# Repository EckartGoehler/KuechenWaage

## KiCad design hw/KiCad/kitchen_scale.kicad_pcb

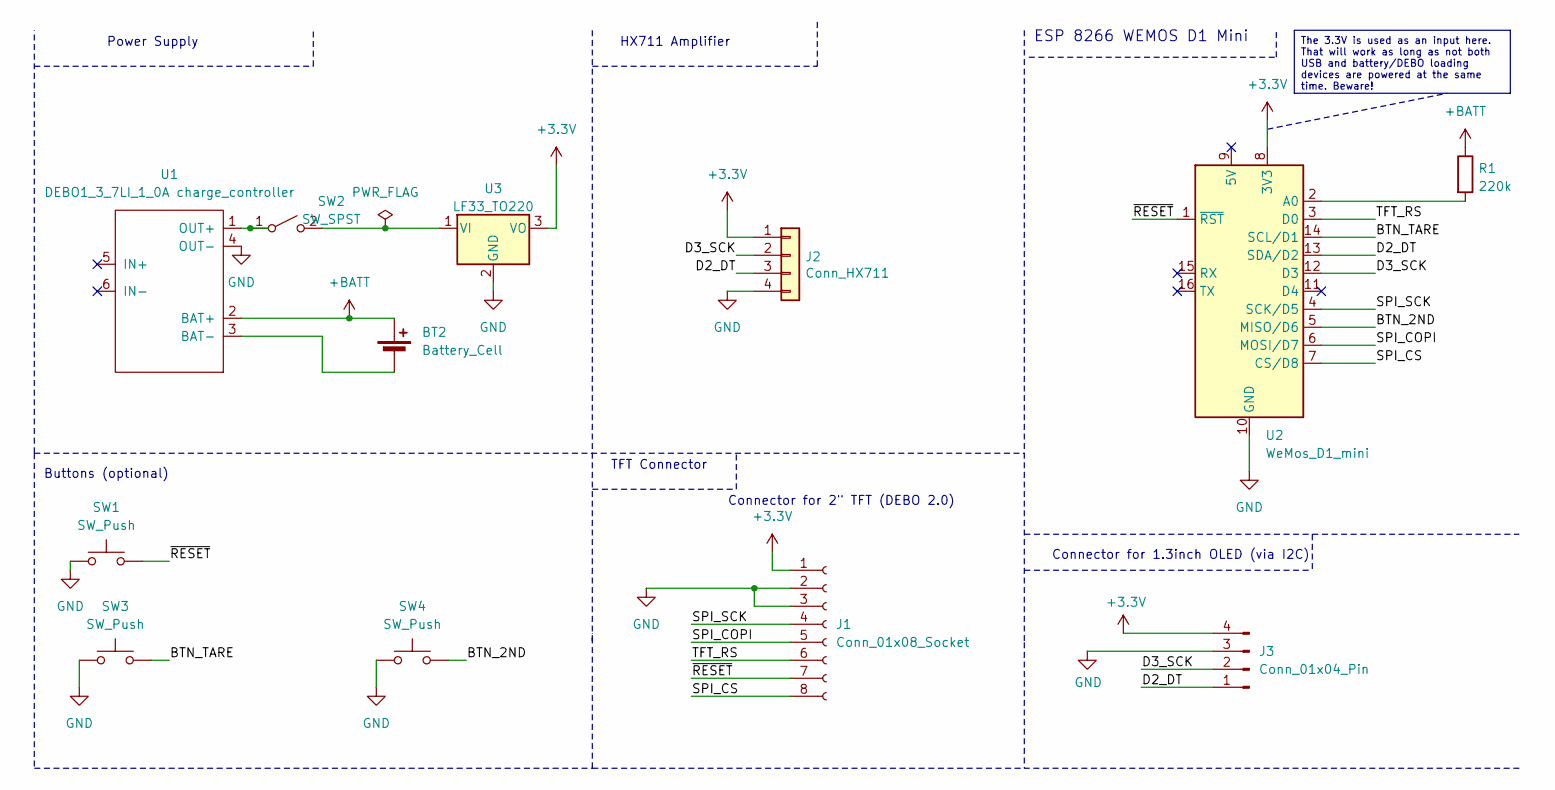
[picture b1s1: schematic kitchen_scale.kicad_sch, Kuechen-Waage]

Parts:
BT2: Battery_Cell; PinHeader_1x02_P2.54mm_Vertical
J1: Conn_01x08_Socket; PinHeader_2x04_P2.54mm_Vertical
J2: Conn_HX711; PinSocket_1x04_P2.54mm_Vertical
J3: Conn_01x04_Pin; PinHeader_1x04_P2.54mm_Vertical
R1: 220k; R_Axial_DIN0207_L6.3mm_D2.5mm_P7.62mm_Horizontal
SW1, SW3, SW4: SW_Push; SW_PUSH-12mm
SW2: SW_SPST; PinSocket_1x02_P2.54mm_Vertical
U1: DEBO1_3_7LI_1_0A charge_controller; DEBO1_3_7LI_1_0A_charge_controller
U2: WeMos_D1_mini; WEMOS_D1_mini_light
U3: LF33_TO220; TO-220-3_Vertical

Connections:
+3.3V: J1.1, J2.1, J3.4, U2.8 (3V3), U3.3 (VO)
+BATT: BT2.1 (+), R1.1, U1.2 (BAT+)
/BTN_2ND: SW4.2, U2.5 (MISO/D6)
/BTN_TARE: SW3.2, U2.14 (SCL/D1)
/D2_DT: J2.3, J3.1, U2.13 (SDA/D2)
/D3_SCK: J2.2, J3.2, U2.12 (D3)
/SPI_COPI: J1.5, U2.6 (MOSI/D7)
/SPI_CS: J1.8, U2.7 (CS/D8)
/SPI_SCK: J1.4, U2.4 (SCK/D5)
/TFT_RS: J1.6, U2.3 (D0)
/~RESET: J1.7, SW1.2, U2.1 (~RST)
GND: J1.2, J1.3, J2.4, J3.3, SW1.1, SW3.1, SW4.1, U1.4 (OUT-), U2.10 (GND), U3.2 (GND)
unnamed: BT2.2 (-), U1.3 (BAT-)
unnamed: SW2.1 (A), U1.1 (OUT+)
unnamed: SW2.2 (B), U3.1 (VI)
unnamed: R1.2, U2.2 (A0)

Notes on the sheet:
The 3.3V is used as an input here. That will work as long as not both USB and battery/DEBO loading devices are powered at the same time. Beware!
Connector for 2" TFT (DEBO 2.0)
Power Supply
TFT Connector
HX711 Amplifier
ESP 8266 WEMOS D1 Mini
Connector for 1.3inch OLED (via I2C)
Buttons (optional)

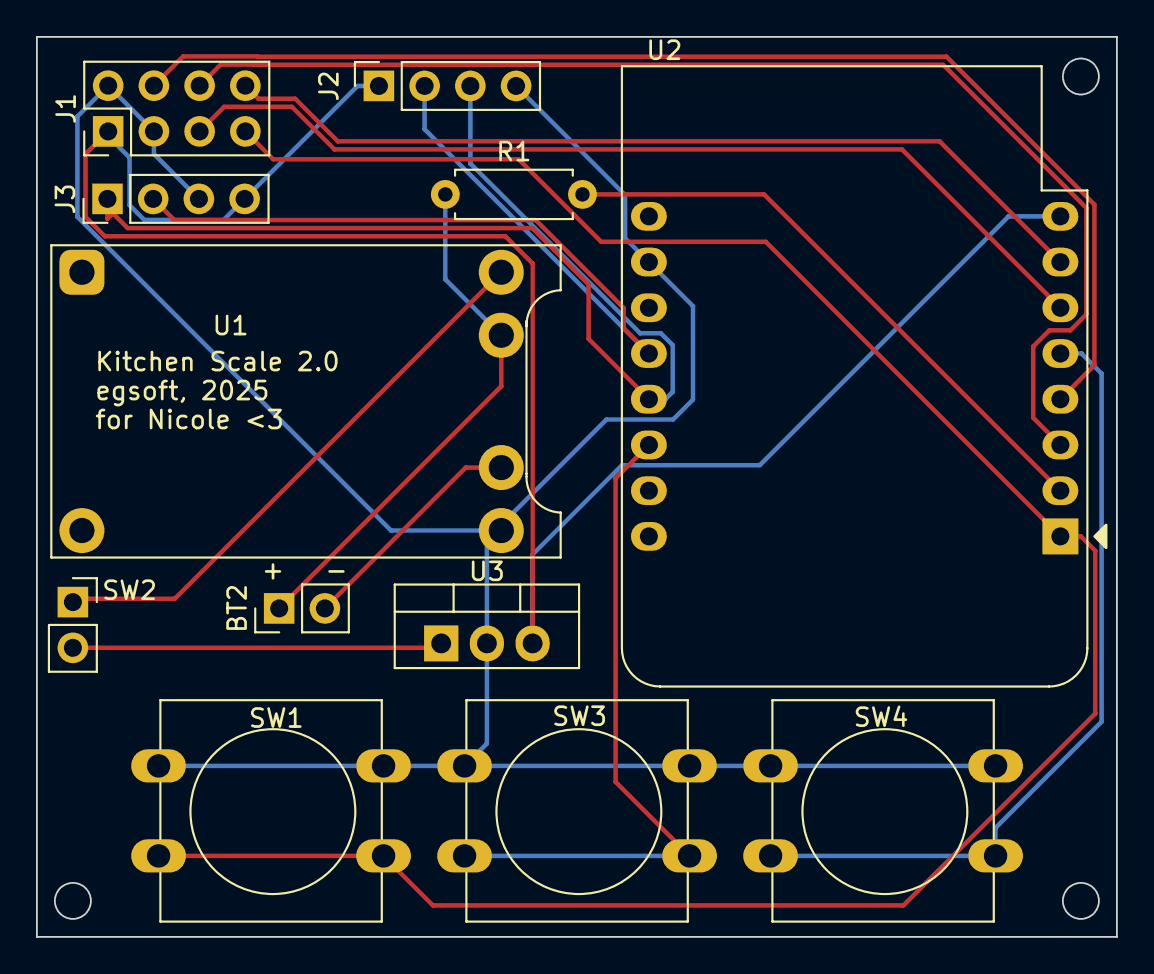
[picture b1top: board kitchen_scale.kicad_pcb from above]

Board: 2 copper layers, 60.0 x 50.0 mm, 12 parts (0 on the bottom side), 16 nets.

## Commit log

2025-11-09 Import latest kitchen scale, still not elaborated
2025-11-09 Change to ESP8266, as needing anyway 3.3V and is smaller.
2025-11-09 Clean up of symbols, added Mine Added buttons and battery charging state
2025-11-09 Add footprints Add first draft of PCB
2025-11-09 Update of fine placement
2025-11-09 Completed wiring
2025-11-09 Add label
2025-11-09 improved routing
2025-11-09 Add mounting holes
2025-11-09 Add battery signs
2025-11-15 Add Hx711 module (not fully connected) for reference
2025-11-22 Add draft of cmake build for a kitchen scale. Compiling but not running properly
2025-11-22 Fix: proper pins (=GPIOs, not the standard ones..), disable watchdog
2025-11-22 Add: Blink with output Fix: Do not disable the watchdog -> will not work properly
2025-11-22 Add: switch to 1.77" AzDelivery display with ST7789 processor. Seems working.
2025-11-23 Include ST77xx in project
2025-11-23 Add: test for 1.77" display Add: provide display output in kitchenscale. Still very draft, but in general working
2025-12-14 Fix: improved display with sensible size and non-flickering output Add: draft of EEPROM (=flash) support, added calibration application. Still not working
2025-12-14 Make calibration application work. Still now satisfying calibration
2025-12-14 Proper EEPROM reading
2025-12-14 Add serial test application
2025-12-14 Make serial scale work properly
2025-12-23 First almost complete version, some small issues: - display not fitting - PCB loose - shift PCB to the left
2025-12-25 Change: moved pcb leftmost -> more space for display connector
2025-12-25 Fix of mounting left pin position
2025-12-25 Add cover of flex cable. Camfer not working for now
2025-12-25 Larger screw cones
2025-12-25 Fix display positions and sizes. To be checked
2025-12-25 display hole fix 2 (x shifted)
2025-12-25 Add top shell mounting cylinder
2025-12-25 Fix: extended display hole left 0.5mm
2025-12-25 Add battery keeper
2025-12-25 Round corners
2025-12-25 Add unicorn logo
2025-12-25 shifted and scaled unicorn
2025-12-25 Fix: removed accidental face from screw mounting part
2025-12-26 Add top pan
2025-12-26 Tried to fix display pin hole -> not working so far.
2025-12-26 Reduced tare time
2025-12-26 Add: tare button functionality
2025-12-26 Add button
2025-12-27 Final adjustments and greetings
2025-12-27 Button with proper length
2025-12-27 Patch by enabling compound for button (it is a single object!)
2026-04-21 Status as delivered
